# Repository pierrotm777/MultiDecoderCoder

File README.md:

# MultiDecoderCoder
 This code is running only with Arduino Uno,Pro Mini ou Pro Micro 
	- Option JetiEx is running only with Pro Micro
	- Option Failsafe is running only with Pro Mini

 Decoder for maxi 16 servos for signals protols:
 - PPM based on libraries RC Navy https://github.com/RC-Navy/DigisparkArduinoIntegration/tree/master/libraries/DigisparkTinyCppmReader
 - SBUS based on libraries RC Navy https://github.com/RC-Navy/DigisparkArduinoIntegration/tree/master/libraries/RcBusRx
	A signal's reverse is needed (http://www.ernstc.dk/arduino/sbus.html)
 - IBUS based on librarie RC Navy https://github.com/RC-Navy/DigisparkArduinoIntegration/tree/master/libraries/RcBusRx
 - DSMX based on librarie https://github.com/Quarduino/SpektrumSatellite
 - SRXL based on libraries RC Navy https://github.com/RC-Navy/DigisparkArduinoIntegration/tree/master/libraries/RcBusRx
 - SUMD based on exemple RC Navy https://github.com/RC-Navy/DigisparkArduinoIntegration/tree/master/libraries/RcBusRx
 - JETIEX based on librarie RC Navy https://github.com/RC-Navy/DigisparkArduinoIntegration/tree/master/libraries/RcBusRx

 Coder convert 8 outputs servos PWM in:
 - PPM based on libraries RC Navy (http://p.loussouarn.free.fr/arduino/arduino.html) 
 - SBUS based on libraries RC Navy (http://p.loussouarn.free.fr/arduino/arduino.html) 
 - IBUS

 How to use it:
 When you use your module the first time, you need to configure it.
 For that, you need to connect FTDI module to your Pro Mini board or use the USB port of your Pro Micro board.
 Use the IDE console (115200 bauds and NL and CR).
 You have 3 secondes for use the ENTER key.
 After that, without new settings, the code start in PPM mode.
   
 The console will return:
 
	Version:0.40
	Wait Return...
	
	Starting without configuration
	Decoder in use
	Failsafe is Off
	8 outputs mode (Use D2-D9)
	PPM mode in use

 If you use the ENTER key before the 3s, you enter in the Configuration mode.
 
	Version:0.40
	Wait Return.
	
	Configuration mode is actived
	Decoder in use
	Failsafe is Off
	8 outputs mode (Use D2-D9)
	PPM mode in use

 Enter 'h' key (without cote) for the help.
 
	h Help
	q quit
	0 set Decoder mode
	1 set Coder mode
	n set 8/16 outputs mode
	r first 8 outputs changed
	p set PPM mode
	s set SBUS mode
	i set IBUS mode
	d set DSMX mode
	m set SRLX mode
	u set SUMD mode
	j set JETIEx mode
	f set Failsafe values
	
 The DECODER mode know the protocols PPM, SBUS, IBUS, DSMX, SRLX, SUMD and JETIEx (Pro Micro only).
 The CODER mode know the protocols PPM and SBUS only.
 
 How to connect your module:
 
 - In DECODER mode, use the pin RX as input and VCC,GND as power.
 Use D2 to D9 and D10 to D13, A0 to A3 as PWM output.
 - In CODER mode, use the pin 11 as ouput and VCC,GNS as power.
 Use D2 to D9 and D10 to D13 as PWM input.

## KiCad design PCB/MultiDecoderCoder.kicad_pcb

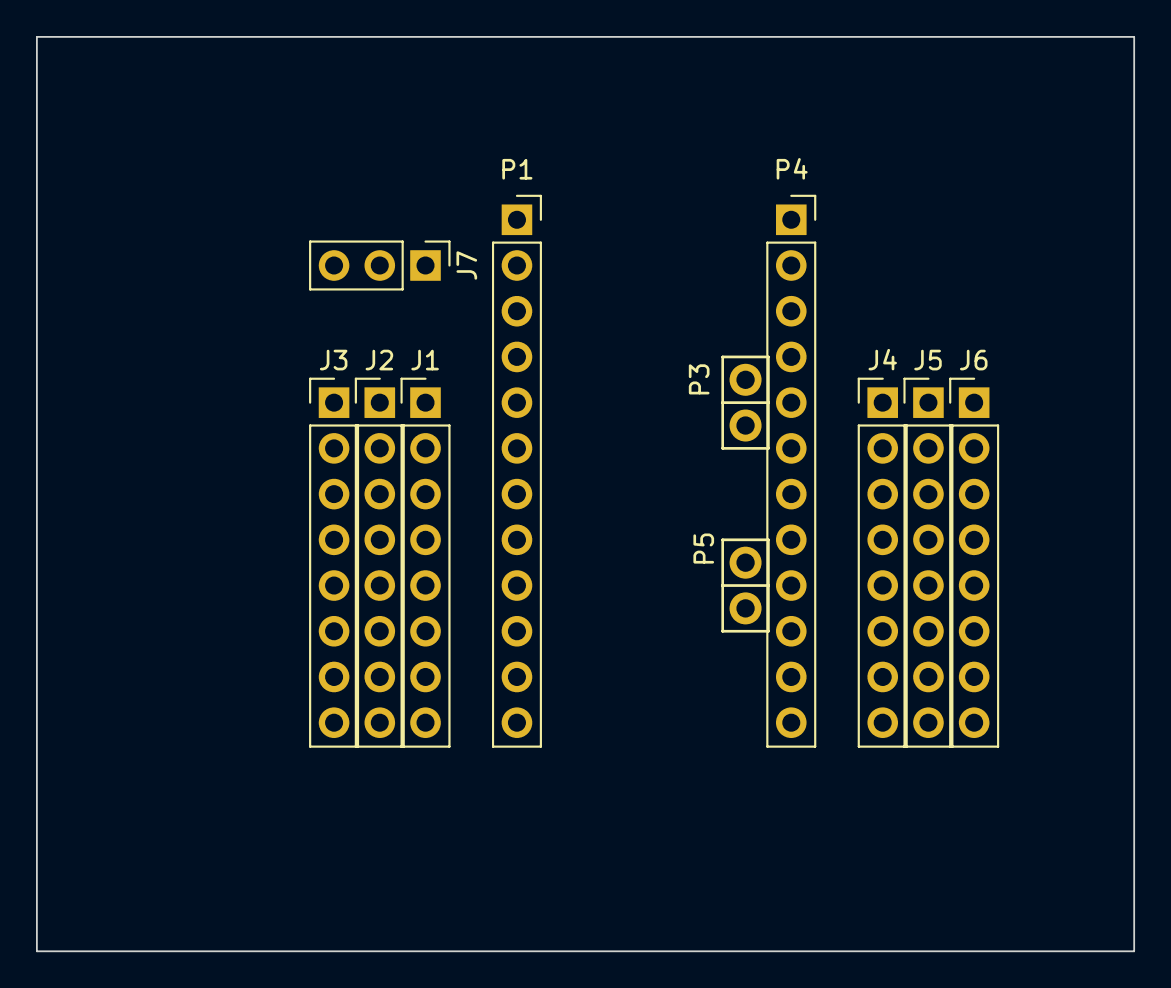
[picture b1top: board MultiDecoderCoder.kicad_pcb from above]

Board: 2 copper layers, 61.0 x 50.8 mm, 11 parts (0 on the bottom side), 19 nets, no tracks yet.

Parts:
J1: Ch1_8; PinHeader_1x08_P2.54mm_Vertical
J2: Ch1_8V+; PinHeader_1x08_P2.54mm_Vertical
J3: Ch1_8V-; PinHeader_1x08_P2.54mm_Vertical
J4: Ch9_16; PinHeader_1x08_P2.54mm_Vertical
J5: Ch9_16V+; PinHeader_1x08_P2.54mm_Vertical
J6: Ch9_16V-; PinHeader_1x08_P2.54mm_Vertical
J7: Conn_01x03; PinHeader_1x03_P2.54mm_Vertical
P1: Digital; PinSocket_1x12_P2.54mm_Vertical
P3, P5: ADC; Socket_Strip_Arduino_1x02
P4: Analog; PinSocket_1x12_P2.54mm_Vertical

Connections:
+5V: J2.1, J2.2, J2.3, J2.4, J2.5, J2.6, J2.7, J2.8, J5.1, J5.2, J5.3, J5.4, J5.5, J5.6, J5.7, J5.8, J7.2
/A0: J4.4, P4.8
/A1: J4.3, P4.7
/A2: J4.2, P4.6
/A3: J4.1, P4.5
/D0(RX): J7.1, P1.2
/D2: J1.1, P1.5
/D3: J1.2, P1.6
/D4: J1.3, P1.7
/D5: J1.4, P1.8
/D6: J1.5, P1.9
/D7: J1.6, P1.10
/D8: J1.7, P1.11
/D9: J1.8, P1.12
/D10: J4.8, P4.12
/D11: J4.7, P4.11
/D12: J4.6, P4.10
/D13: J4.5, P4.9
GND: J3.1, J3.2, J3.3, J3.4, J3.5, J3.6, J3.7, J3.8, J6.1, J6.2, J6.3, J6.4, J6.5, J6.6, J6.7, J6.8, J7.3, P1.4, P4.3

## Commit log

2020-03-22 Add Arduino main code
2020-03-22 Add Libraries for MultiDecoder
2020-03-22 Update Readme.md file
2020-03-22 Add RCNAVY libraries
2020-05-09 Replace lib by Rc Navy libs
2020-05-20 Remove old libraries
2020-05-20 Add PCB files
2020-08-07 Add MultiWii decod
